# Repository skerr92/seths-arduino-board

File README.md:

# seths-arduino-board
Just a repository for the PCB design and schematic for a custom Arduino Board.

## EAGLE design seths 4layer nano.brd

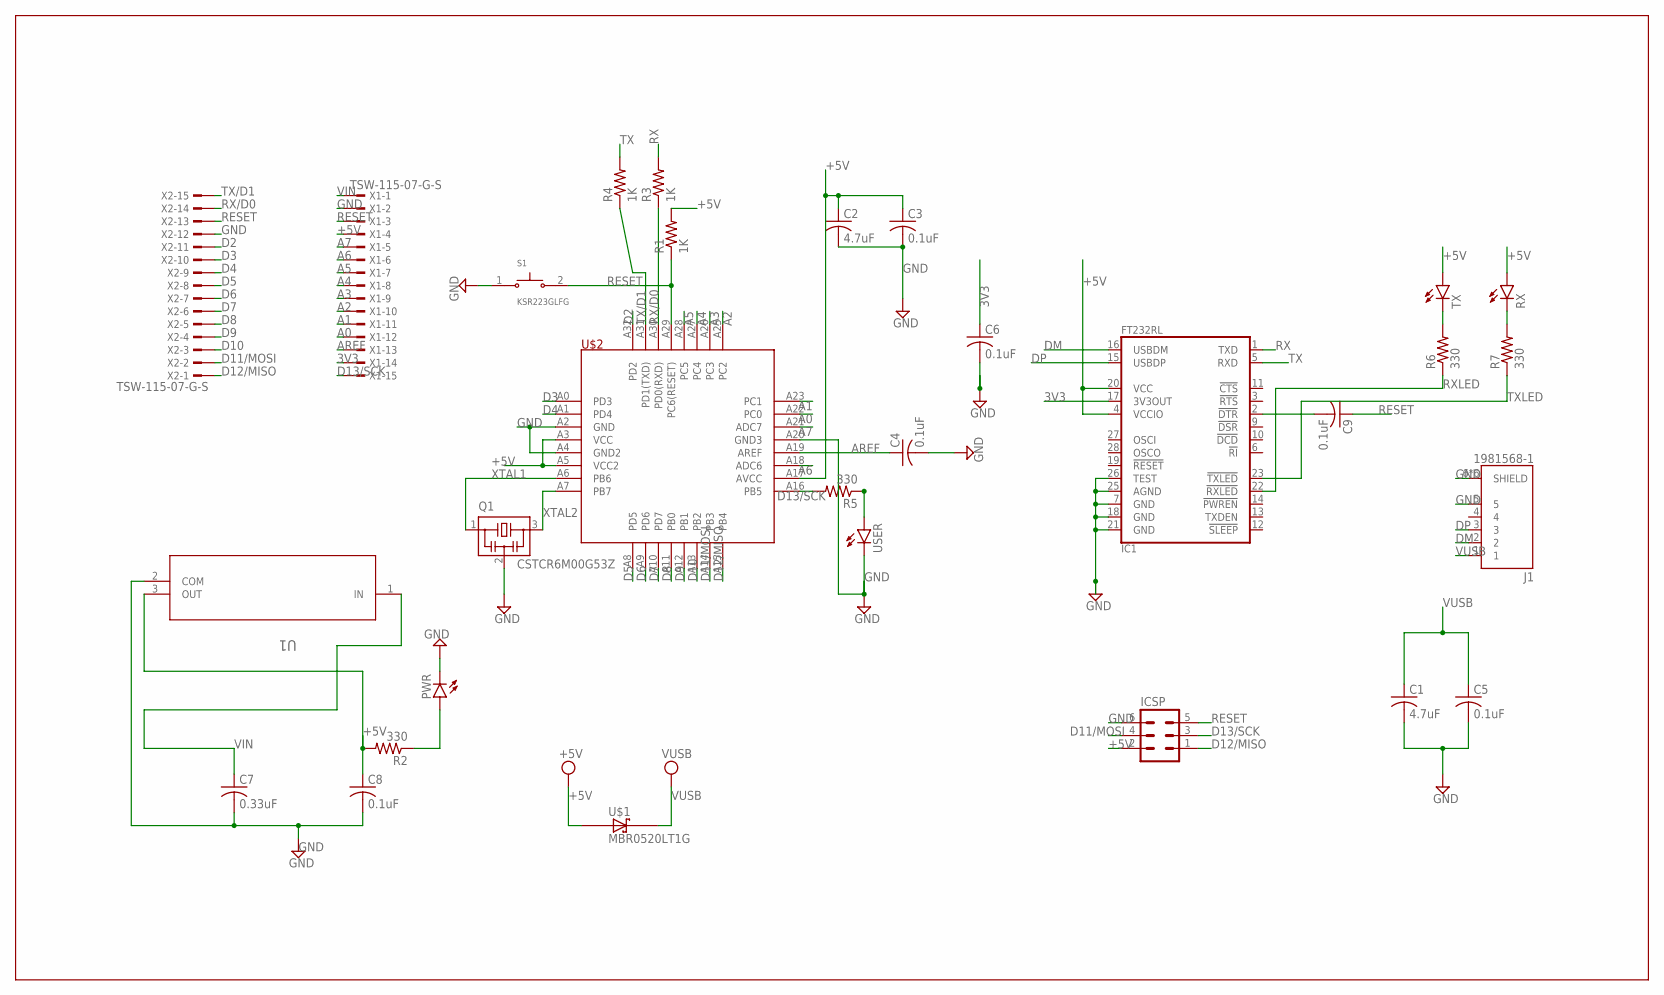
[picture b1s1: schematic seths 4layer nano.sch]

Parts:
C1, C2: 4.7uF; C1206
C3, C4, C5, C6, C8, C9: 0.1uF; C0603
C7: 0.33uF; C0603
IC1: FT232RL; SSOP28-LD
ICSP: MA03-2
J1: 1981568-1; TE_1981568-1
PWR: RED_POWER; CHIP-LED0603
Q1: CSTCR6M00G53Z; CSTCR6M
R1, R3, R4: 1K; R0603
R2, R5, R6, R7: 330; R0603
RX: RED_TX; CHIP-LED0603
S1: KSR223GLFG; SW_KSR223GLFG
TX: RED_RX; CHIP-LED0603
U1: UA78M05CDCYRDCY4-L; DCY4-L
U$1: MBR0520LT1G; SOD3716X117(SOD-123)
U$2: ATMEGA328P; TQFP32
USER: Amber_L; CHIP-LED0603
X1, X2: TSW-115-07-G-S; TSW-115-XX-G-S

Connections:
3V3: C6.1, IC1.17 (3V3OUT), X1.14
+5V: C2.1, C3.1, C8.1, IC1.4 (VCCIO), IC1.20 (VCC), ICSP.2, R1.2, R2.2, RX.A, TX.A, U1.3 (OUT), U$1.2 (A), U$2.A3 (VCC), U$2.A5 (VCC2), U$2.A17 (AVCC), X1.4
A0: U$2.A22 (PC0), X1.12
A1: U$2.A23 (PC1), X1.11
A2: U$2.A25 (PC2), X1.10
A3: U$2.A26 (PC3), X1.9
A4: U$2.A27 (PC4), X1.8
A5: U$2.A28 (PC5), X1.7
A6: U$2.A18 (ADC6), X1.6
A7: U$2.A21 (ADC7), X1.5
AREF: C4.1, U$2.A19 (AREF), X1.13
D2: U$2.A32 (PD2), X2.11
D3: U$2.A0 (PD3), X2.10
D4: U$2.A1 (PD4), X2.9
D5: U$2.A8 (PD5), X2.8
D6: U$2.A9 (PD6), X2.7
D7: U$2.A10 (PD7), X2.6
D8: U$2.A11 (PB0), X2.5
D9: U$2.A12 (PB1), X2.4
D10: U$2.A13 (PB2), X2.3
D11/MOSI: ICSP.4, U$2.A14 (PB3), X2.2
D12/MISO: ICSP.1, U$2.A15 (PB4), X2.1
D13/SCK: ICSP.3, R5.2, U$2.A16 (PB5), X1.15
DM: IC1.16 (USBDM), J1.2
DP: IC1.15 (USBDP), J1.3
GND: C1.2, C2.2, C3.2, C4.2, C5.2, C6.2, C7.2, C8.2, IC1.7 (GND), IC1.18 (GND), IC1.21 (GND), IC1.25 (AGND), IC1.26 (TEST), ICSP.6, J1.5, J1.6 (SHIELD), J1.7 (SHIELD), J1.8 (SHIELD), J1.9 (SHIELD), J1.10 (SHIELD), J1.11 (SHIELD), PWR.C, Q1.2, S1.1, U1.2 (COM), U$2.A2 (GND), U$2.A4 (GND2), U$2.A20 (GND3), USER.C, X1.2, X2.12
unnamed: R5.1, USER.A
unnamed: R6.2, TX.C
unnamed: R7.2, RX.C
unnamed: C9.2, IC1.2 (!DTR)
unnamed: PWR.A, R2.1
RESET: C9.1, ICSP.5, R1.1, S1.2, U$2.A29 (PC6(RESET)), X1.3, X2.13
RX: IC1.1 (TXD), R3.2
RX/D0: R3.1, U$2.A30 (PD0(RXD)), X2.14
RXLED: IC1.22 (!RXLED), R6.1
TX: IC1.5 (RXD), R4.2
TX/D1: R4.1, U$2.A31 (PD1(TXD)), X2.15
TXLED: IC1.23 (!TXLED), R7.1
VIN: C7.1, U1.1 (IN), X1.1
VUSB: C1.1, C5.1, J1.1, U$1.1 (C)
XTAL1: Q1.1, U$2.A6 (PB6)
XTAL2: Q1.3, U$2.A7 (PB7)

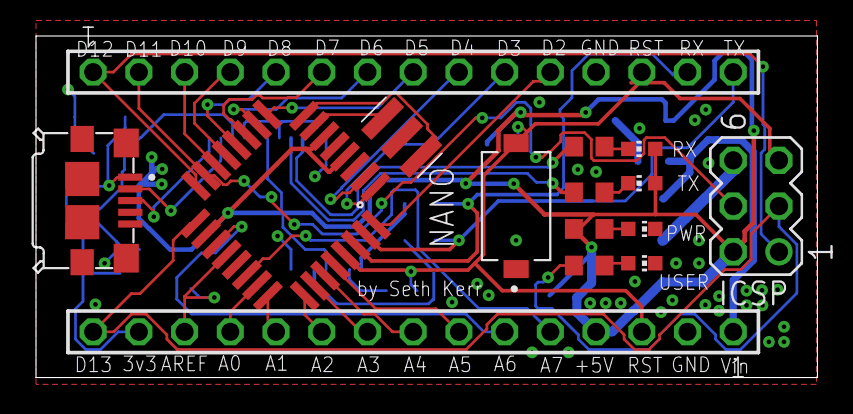
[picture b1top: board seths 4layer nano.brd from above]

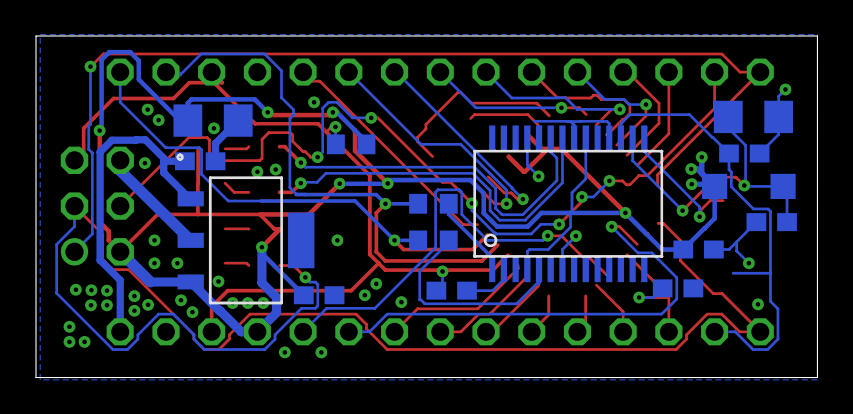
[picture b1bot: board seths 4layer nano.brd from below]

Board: 2 copper layers, 43.4 x 19.0 mm, 30 parts (15 on the bottom side), 42 nets.

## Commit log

2020-07-30 Add files via upload
    updating this since it hasn't been in a while.
2020-08-27 updating CAM files
    updating cam files
2020-08-27 updating schematic and BRD files
    updating the schematic and board files.
